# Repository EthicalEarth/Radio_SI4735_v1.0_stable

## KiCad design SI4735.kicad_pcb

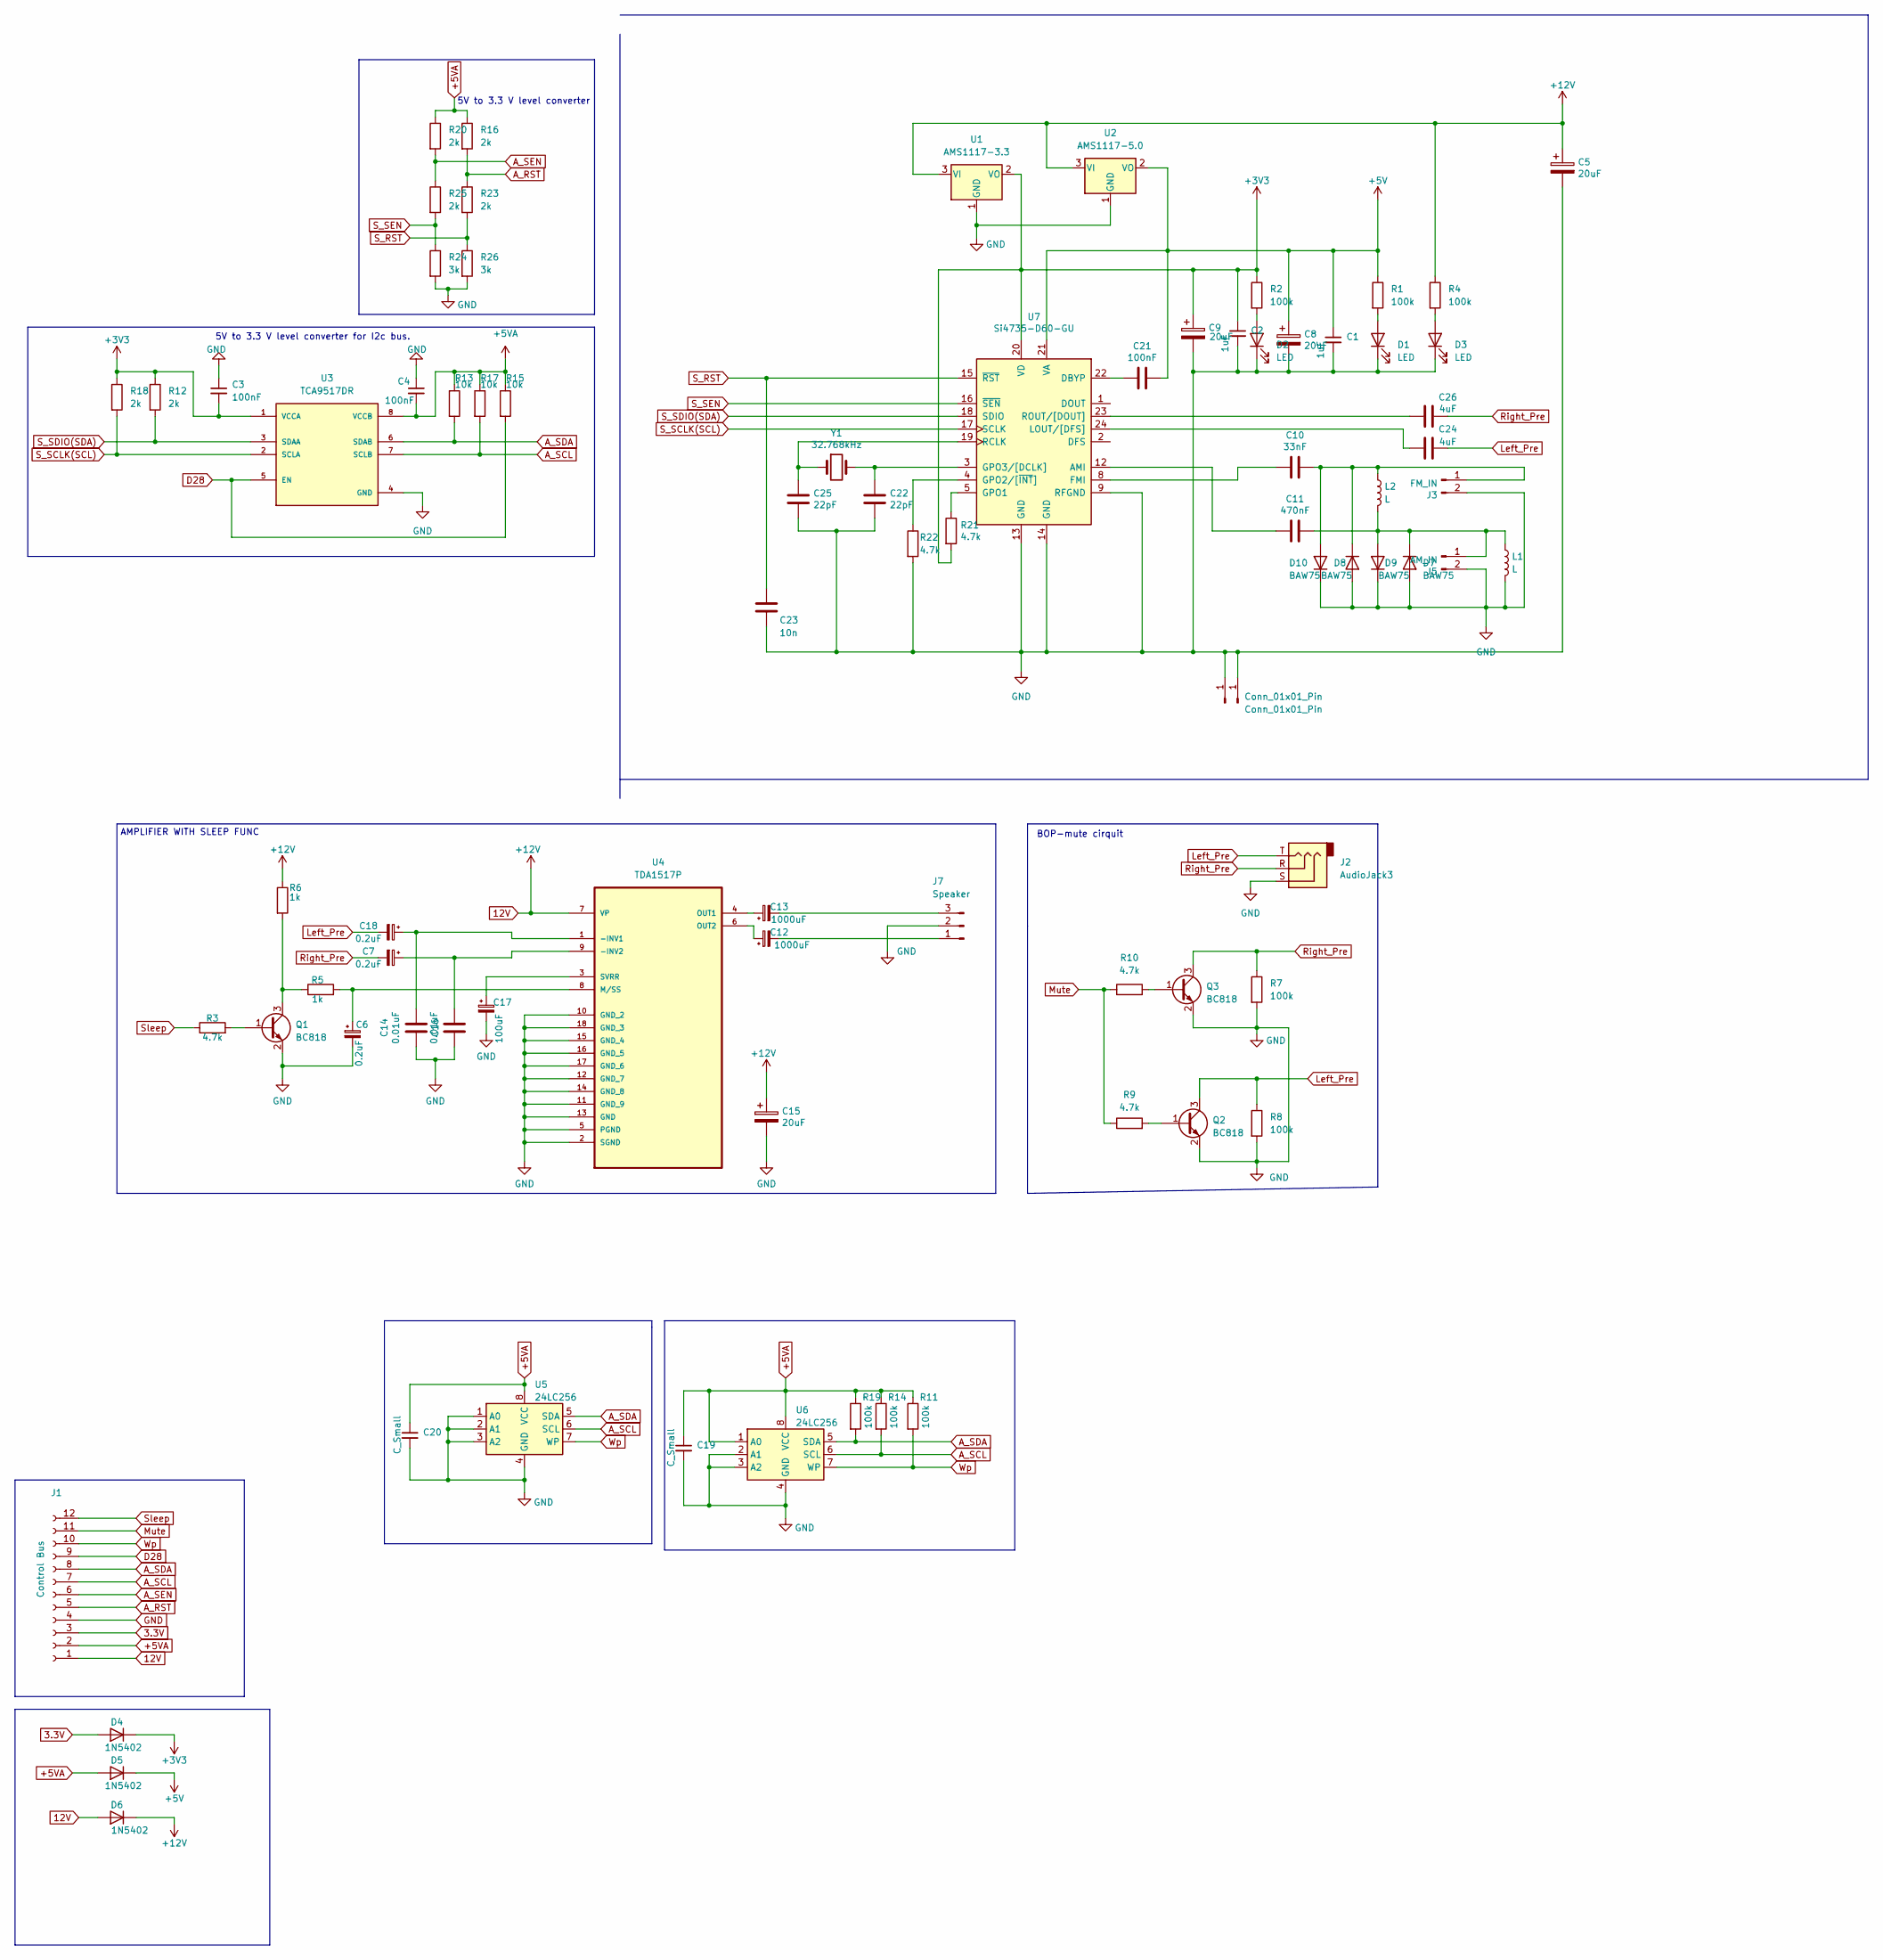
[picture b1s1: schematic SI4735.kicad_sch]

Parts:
C1, C2: 1uF; C_1206_3216Metric_Pad1.33x1.80mm_HandSolder
C3, C4, C21: 100nF; C_1206_3216Metric
C5, C8, C9: 20uF; CP_Radial_D5.0mm_P2.00mm
C6, C7, C18: 0.2uF; CP_Radial_D4.0mm_P2.00mm
C10: 33nF; C_1206_3216Metric
C11: 470nF; C_1206_3216Metric
C12, C13: 1000uF; CP_Radial_D8.0mm_P3.80mm
C14, C16: 0.01uF; C_1206_3216Metric
C15: 20uF; C_1206_3216Metric
C17: 100uF; CP_Radial_D5.0mm_P2.00mm
C19, C20: C_Small; C_1206_3216Metric_Pad1.33x1.80mm_HandSolder
C22, C25: 22pF; C_1206_3216Metric
C23: 10n; C_1206_3216Metric
C24, C26: 4uF; C_Disc_D3.0mm_W1.6mm_P2.50mm
D1, D2, D3: LED; LED_1206_3216Metric
D4, D5, D6: 1N5402; D_1206_3216Metric
D7, D8, D9, D10: BAW75; D_1206_3216Metric
J1: Control Bus; PinSocket_1x12_P2.54mm_Vertical
J2: AudioJack3; Jack_3.5mm_CUI_SJ-3523-SMT_Horizontal
J3: FM_IN; SMA_Amphenol_901-143_Horizontal
J4, J6: Conn_01x01_Pin; PinSocket_1x01_P1.27mm_Vertical
J5: AM_IN; SMA_Amphenol_901-143_Horizontal
J7: Speaker; PinSocket_1x03_P2.54mm_Vertical
L1: L; L_Axial_L7.0mm_D3.3mm_P5.08mm_Vertical_Fastron_MICC
L2: L; L_Radial_D6.0mm_P4.00mm
Q1, Q2, Q3: BC818; SOT-23
R1, R2, R4, R7, R8, R11, R14, R19: 100k; R_1206_3216Metric
R3, R9, R10, R21, R22: 4.7k; R_1206_3216Metric
R5, R6: 1k; R_1206_3216Metric
R12, R16, R18, R20, R23, R25: 2k; R_1206_3216Metric
R13, R15, R17: 10k; R_1206_3216Metric
R24, R26: 3k; R_1206_3216Metric
U1: AMS1117-3.3; SOT-223-3_TabPin2
U2: AMS1117-5.0; SOT-223-3_TabPin2
U3: TCA9517DR; SOIC127P599X175-8N; PARTREV D
U4: TDA1517P; DIP254P762X470-18; MPN TDA1517P/N3,112
U5, U6: 24LC256; SOIC-8_3.9x4.9mm_P1.27mm
U7: Si4735-D60-GU; SSOP-24_3.9x8.7mm_P0.635mm
Y1: 32.768kHz; Crystal_C38-LF_D3.0mm_L8.0mm_Horizontal

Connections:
3.3V: D4.2 (A), J1.3
12V: C5.1, C15.1, D6.1 (K), D6.2 (A), J1.1, R4.1, R6.1, U1.3 (VI), U2.3 (VI), U4.7 (VP)
+3V3: C2.1, C3.2, C9.1, D4.1 (K), R2.1, R12.1, R18.1, R21.2, U1.2 (VO), U3.1 (VCCA), U7.20 (VD)
+5V: C1.1, C8.1, C21.1, D5.1 (K), R1.1, U2.2 (VO), U7.21 (VA)
+5VA: C4.2, C19.1, C20.1, D5.2 (A), J1.2, R11.1, R13.1, R14.1, R15.1, R16.1, R17.1, R19.1, R20.1, U3.8 (VCCB), U5.8 (VCC), U6.1 (A0), U6.8 (VCC)
A_RST: J1.5, R16.2, R23.1
A_SCL: J1.7, R14.2, R17.2, U3.7 (SCLB), U5.6 (SCL), U6.6 (SCL)
A_SDA: J1.8, R13.2, R19.2, U3.6 (SDAB), U5.5 (SDA), U6.5 (SDA)
A_SEN: J1.6, R20.2, R25.1
D28: J1.9, R15.2, U3.5 (EN)
GND: C1.2, C2.2, C3.1, C4.1, C5.2, C6.2, C8.2, C9.2, C14.2, C15.2, C16.2, C17.2, C19.2, C20.2, C22.2, C23.2, C25.2, D1.1 (K), D2.1 (K), D3.1 (K), D7.2 (A), D8.2 (A), D9.1 (K), D10.1 (K), J1.4, J2.S, J3.2, J4.1, J5.2, J6.1, J7.2, L1.2, Q1.2 (E), Q2.2 (E), Q3.2 (E), R7.2, R8.2, R22.2, R24.2, R26.2, U1.1 (GND), U2.1 (GND), U3.4 (GND), U4.2 (SGND), U4.5 (PGND), U4.10 (GND_2), U4.11 (GND_9), U4.12 (GND_7), U4.13 (GND), U4.14 (GND_8), U4.15 (GND_4), U4.16 (GND_5), U4.17 (GND_6), U4.18 (GND_3), U5.1 (A0), U5.2 (A1), U5.3 (A2), U5.4 (GND), U6.2 (A1), U6.3 (A2), U6.4 (GND), U7.9 (RFGND), U7.13 (GND), U7.14 (GND)
Left_Pre: C18.2, C24.1, J2.T, Q2.3 (C), R8.1
Mute: J1.11, R9.1, R10.1
unnamed: D1.2 (A), R1.2
unnamed: D2.2 (A), R2.2
unnamed: D3.2 (A), R4.2
unnamed: C11.1, D7.1 (K), D9.2 (A), J5.1, L1.1, L2.2
unnamed: C10.1, D8.1 (K), D10.2 (A), J3.1, L2.1
unnamed: C12.2, J7.1
unnamed: C13.2, J7.3
unnamed: Q1.1 (B), R3.2
unnamed: Q1.3 (C), R5.1, R6.2
unnamed: Q2.1 (B), R9.2
unnamed: Q3.1 (B), R10.2
unnamed: C14.1, C18.1, U4.1 (-INV1)
unnamed: C7.1, C16.1, U4.9 (-INV2)
unnamed: C6.1, R5.2, U4.8 (M/SS)
unnamed: C13.1, U4.4 (OUT1)
unnamed: C12.1, U4.6 (OUT2)
unnamed: C17.1, U4.3 (SVRR)
unnamed: C11.2, U7.12 (AMI)
unnamed: C21.2, U7.22 (DBYP)
unnamed: C10.2, U7.8 (FMI)
unnamed: R21.1, U7.5 (GPO1)
unnamed: R22.1, U7.4 (GPO2/[~INT])
unnamed: C22.1, U7.3 (GPO3/[DCLK]), Y1.2
unnamed: C24.2, U7.24 (LOUT/[DFS])
unnamed: C25.1, U7.19 (RCLK), Y1.1
unnamed: C26.2, U7.23 (ROUT/[DOUT])
Right_Pre: C7.2, C26.1, J2.R, Q3.3 (C), R7.1
S_RST: C23.1, R23.2, R26.1, U7.15 (~RST)
S_SCLK(SCL): R18.2, U3.2 (SCLA), U7.17 (SCLK)
S_SDIO(SDA): R12.2, U3.3 (SDAA), U7.18 (SDIO)
S_SEN: R24.1, R25.2, U7.16 (~SEN)
Sleep: J1.12, R3.1
Wp: J1.10, R11.2, U5.7 (WP), U6.7 (WP)

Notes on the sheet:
5V to 3.3 V level converter for I2c bus.
5V to 3.3 V level converter
BOP-mute cirquit
AMPLIFIER WITH SLEEP FUNC

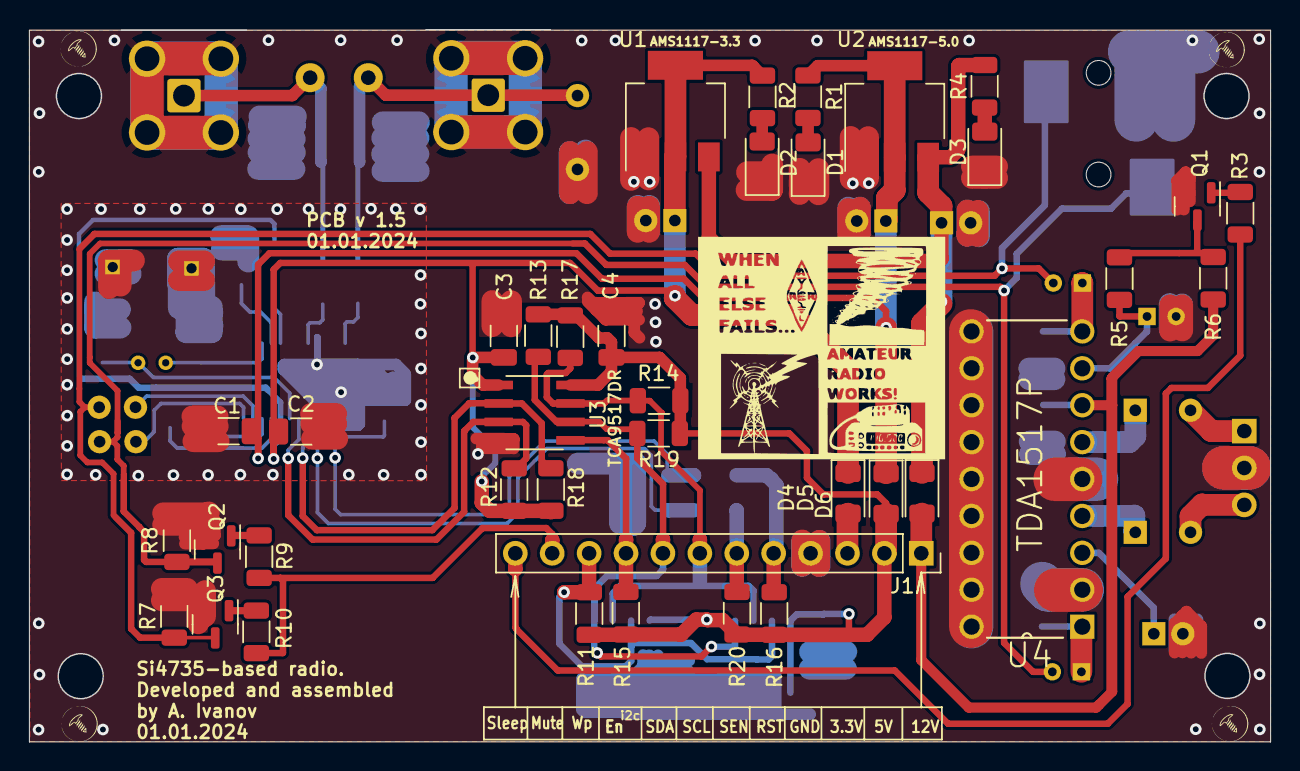
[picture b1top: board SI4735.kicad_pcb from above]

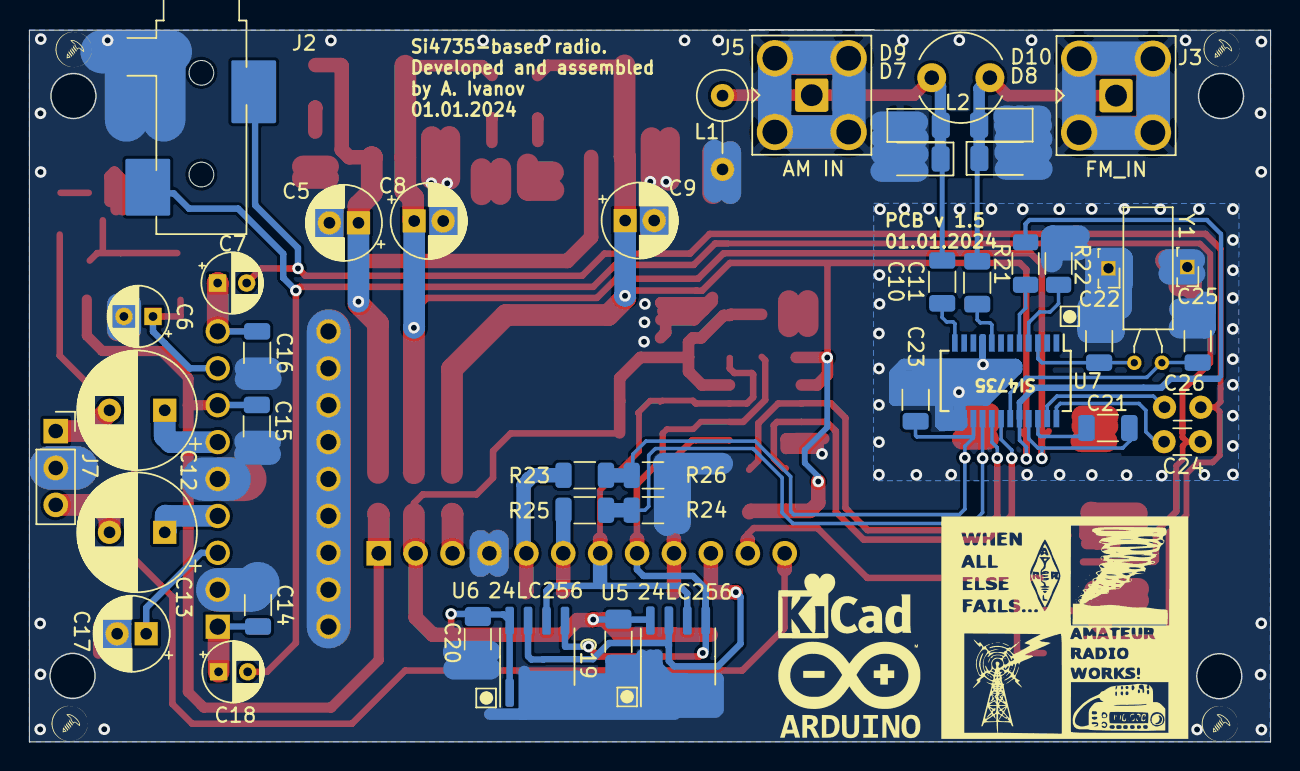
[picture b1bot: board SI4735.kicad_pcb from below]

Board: 2 copper layers, 85.4 x 49.0 mm, 82 parts (44 on the bottom side), 46 nets.

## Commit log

2024-03-23 INIT
2024-03-27 restoring
2024-03-27 restoring..
